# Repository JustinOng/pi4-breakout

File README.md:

Hat template from [xesscorp/RPi_Hat_Template](https://github.com/xesscorp/RPi_Hat_Template).

- 4x connectors for I2C, silkscreen is for KF2510 (or KK 254)
- `GPIO3` (`I2C_SCL`) is connected to a button because grounding it will boot up the Pi after a shutdown (see [`WAKE_ON_GPIO`](https://www.raspberrypi.org/documentation/hardware/raspberrypi/bcm2711_bootloader_config.md))
- `GPIO17` is another arbitrary pin configured to shutdown the Pi when grounded (`dtoverlay=gpio-shutdown,gpio_pin=17` in `/boot/config.txt`)
- Surprisingly, connecting these two pins together and grounding them will startutp/shutdown the Pi, even though `SCL` is pulled low as part of I2C operation. There has been some anecdotal evidence [here](https://www.raspberrypi.org/forums/viewtopic.php?p=1565264#p1565264). Perhaps the deboucing on the shutdown overlay prevents it from triggering?
- `GPIO5` has an LED connected to it - configuring cron to set this pin `HIGH` on boot essentially makes this an indicator for whether the Pi is powered on (note that this pin turns off before the Pi is fully off - a Raspberry Pi 4B has been observed to still be blinking its `ACT` LED when `GPIO5` turns off). Probably a good idea to wait for the `ACT` LED to stop blinking before cutting power.

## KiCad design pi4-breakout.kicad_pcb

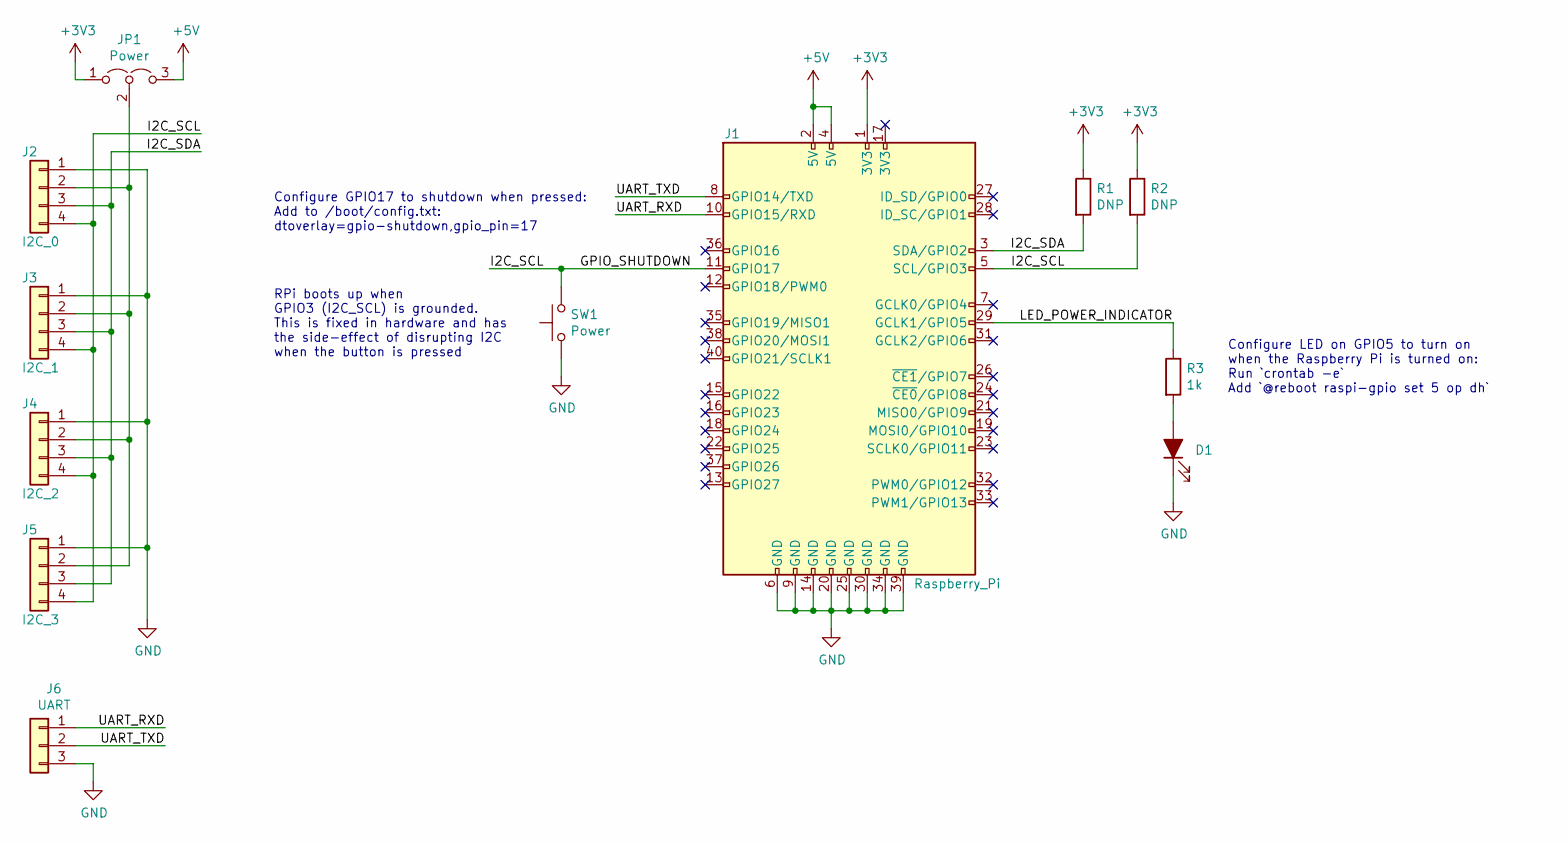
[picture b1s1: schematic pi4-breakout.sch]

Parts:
D1: LED_ALT; D_0603_1608Metric
J1: Raspberry_Pi; Pin_Header_Straight_2x20
J2: I2C_0; Molex_KK-254_AE-6410-04A_1x04_P2.54mm_Vertical
J3: I2C_1; Molex_KK-254_AE-6410-04A_1x04_P2.54mm_Vertical
J4: I2C_2; Molex_KK-254_AE-6410-04A_1x04_P2.54mm_Vertical
J5: I2C_3; Molex_KK-254_AE-6410-04A_1x04_P2.54mm_Vertical
J6: UART; PinHeader_1x03_P2.54mm_Vertical
JP1: Power; PinHeader_1x03_P2.54mm_Vertical
R1, R2: DNP; R_0603_1608Metric
R3: 1k; R_0603_1608Metric
SW1: Power; SW_PUSH_6mm

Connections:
+3V3: J1.1 (3V3), JP1.1 (A), R1.1, R2.1
+5V: J1.2 (5V), J1.4 (5V), JP1.3 (B)
/GPIO_SHUTDOWN: J1.5 (SCL/GPIO3), J1.11 (GPIO17), J2.4, J3.4, J4.4, J5.4, R2.2, SW1.2
/I2C_SDA: J1.3 (SDA/GPIO2), J2.3, J3.3, J4.3, J5.3, R1.2
/LED_POWER_INDICATOR: J1.29 (GCLK1/GPIO5), R3.1
/UART_RXD: J1.10 (GPIO15/RXD), J6.1
/UART_TXD: J1.8 (GPIO14/TXD), J6.2
GND: D1.1 (K), J1.6 (GND), J1.9 (GND), J1.14 (GND), J1.20 (GND), J1.25 (GND), J1.30 (GND), J1.34 (GND), J1.39 (GND), J2.1, J3.1, J4.1, J5.1, J6.3, SW1.1
unnamed: D1.2 (A), R3.2
unnamed: J2.2, J3.2, J4.2, J5.2, JP1.2 (C)

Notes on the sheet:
Configure GPIO17 to shutdown when pressed: Add to /boot/config.txt: dtoverlay=gpio-shutdown,gpio_pin=17
RPi boots up when GPIO3 (I2C_SCL) is grounded. This is fixed in hardware and has the side-effect of disrupting I2C when the button is pressed
Configure LED on GPIO5 to turn on when the Raspberry Pi is turned on: Run `crontab -e` Add `@reboot raspi-gpio set 5 op dh`

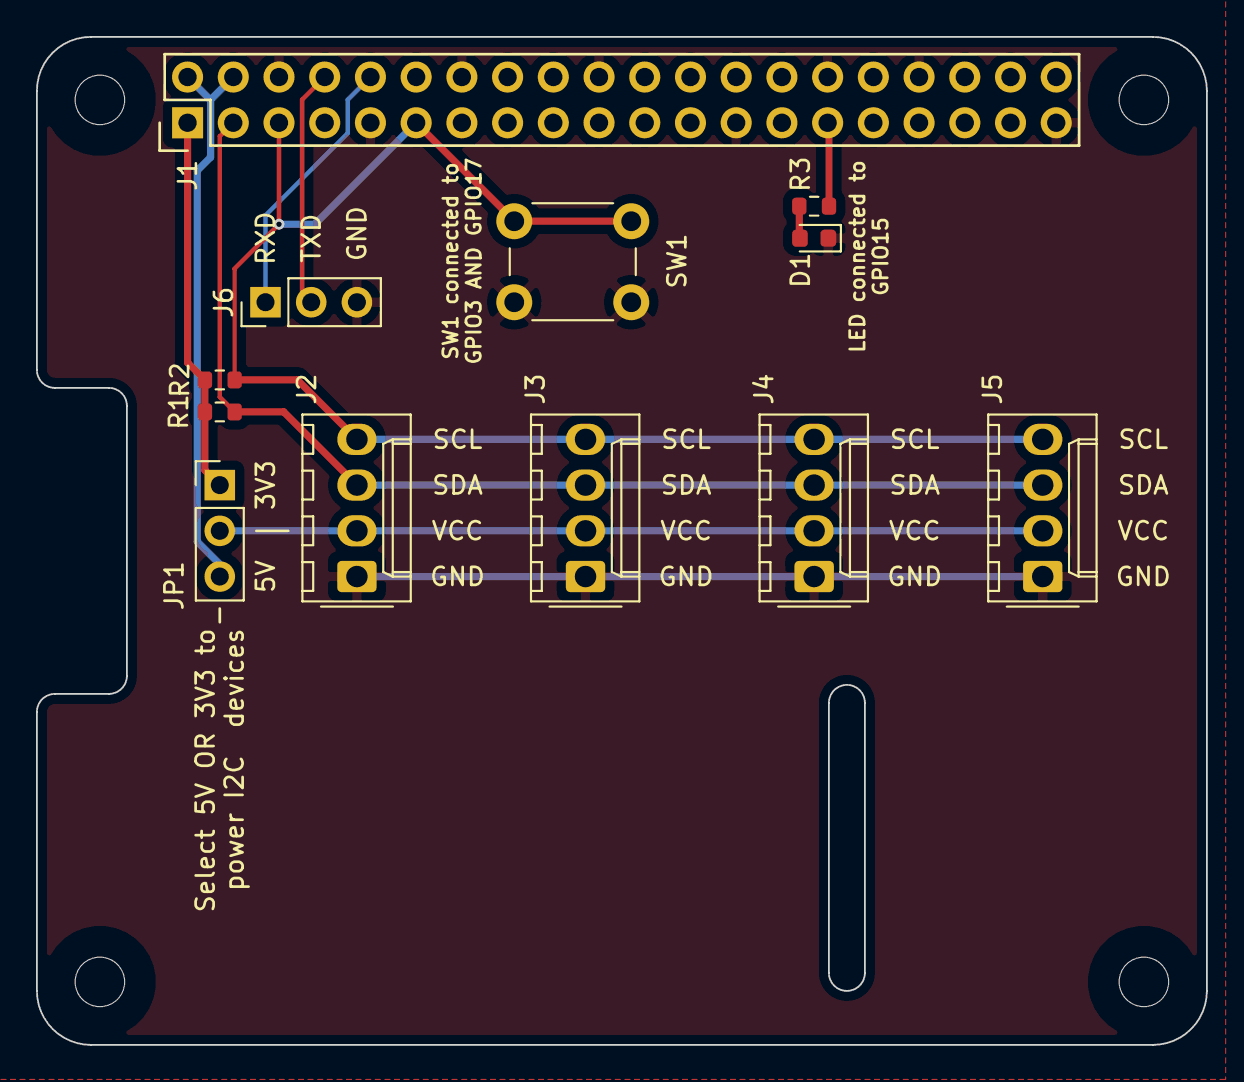
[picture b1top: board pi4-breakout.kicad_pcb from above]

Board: 2 copper layers, 65.0 x 56.0 mm, 12 parts (0 on the bottom side), 10 nets.

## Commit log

2021-05-10 Add README.md
2021-05-12 Export for fabrication
